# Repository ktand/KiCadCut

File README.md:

# About

Generate Silhouette Portrait/Cameo stencil cut file from Kicad PCB file.

Based on the work from [SMTCut](https://github.com/GatCode/SMTCut) and [gerber2graphtec](https://github.com/pmonta/gerber2graphtec)

## Setup

The project uses the [kicad_parser](https://github.com/realthunder/kicad_parser). To get this submodule, after checkout this repository, do

```
git submodule update --init --recursive
```

PDF output (`--pdf`) needs [fpdf2](https://github.com/py-pdf/fpdf2):

```
pip install -r requirements.txt
```

## Basic usage

### Generate cut file
```
kicadcut <kicad_pcb_file> <layer> >file.out
```

### Cuttning blade settings

For a 0.11mm film it appears that a blade setting of 0.15-0.17mm works fine for a 35 degree blade.

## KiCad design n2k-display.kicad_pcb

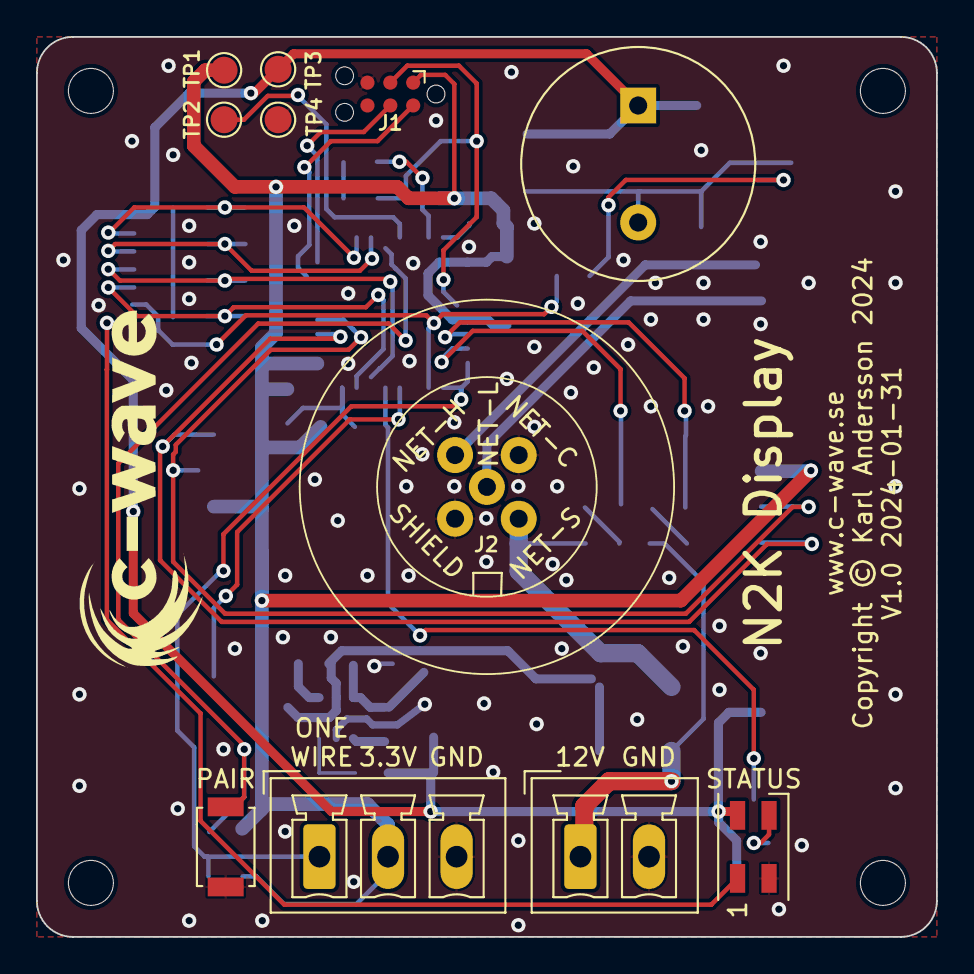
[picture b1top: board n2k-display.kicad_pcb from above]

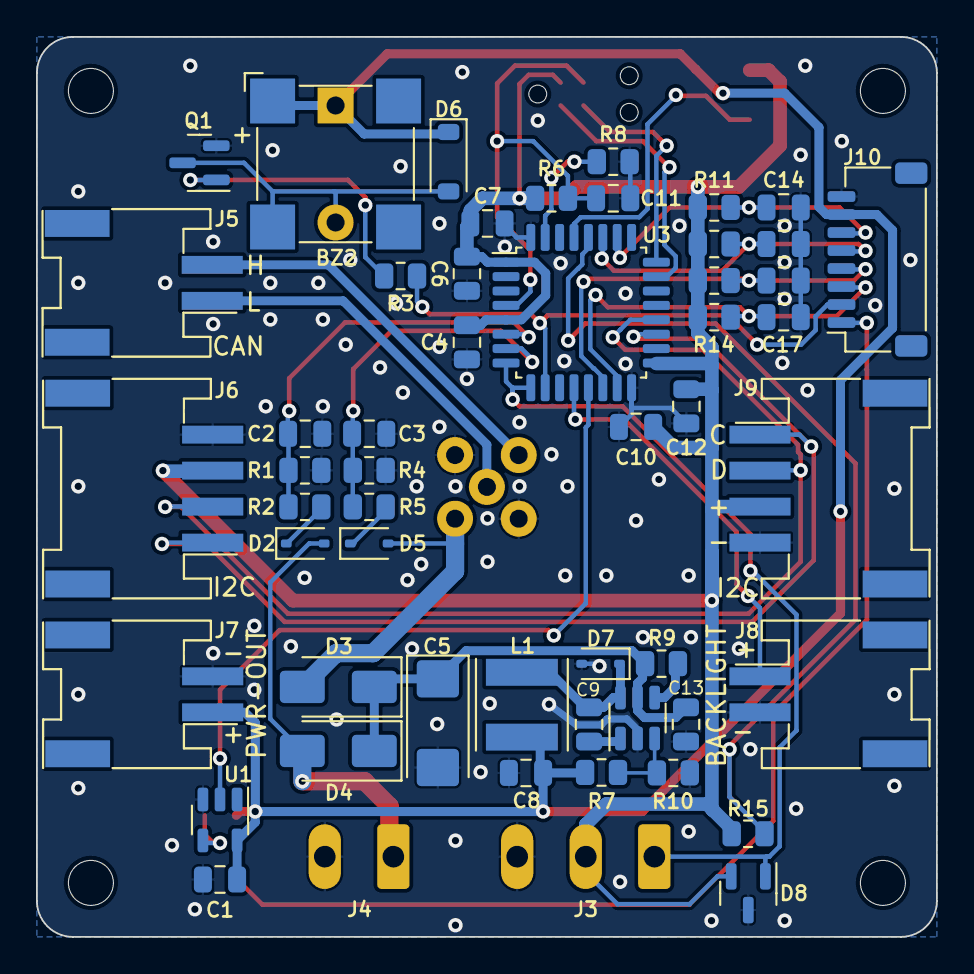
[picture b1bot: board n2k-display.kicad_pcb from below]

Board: 2 copper layers, 50.0 x 50.0 mm, 66 parts (51 on the bottom side), 36 nets.

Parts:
BZ1: 1255; Buzzer_1255
BZ2: CMT-8504-100-SMT-TR; MagneticBuzzer_CUI_CMT-8504-100-SMT
C1, C2, C3, C14, C15, C16, C17: 100n; C_0805_2012Metric
C4: 1uF; C_0805_2012Metric
C5: 100uF; CP_EIA-6032-28_Kemet-C
C6: 10nF; C_0805_2012Metric
C7, C9, C10, C11: 100nF; C_0805_2012Metric
C8: 10uF 16V X7R; C_0805_2012Metric
C12: 4.7uF; C_0805_2012Metric
C13: 10uF 35V X7R; C_0805_2012Metric
D1: SK6812MINI; LED_SK6812MINI_PLCC4_3.5x3.5mm_P1.75mm
D2, D5: SBA130CS-AU; D_SOD-323
D3: US1D; D_SMA
D4: B140-13F; D_SMA
D6: 1N4148W; D_SOD-123
D7: SBA130CS-AU (Schottky Vr > 16V VF >= 1A); D_SOD-323
D8: PESD3V3S2UT; SOT-23
H1, H2, H3, H4: MountingHole; MountingHole_2.5mm
J1: Conn_ARM_SWD_TagConnect_TC2030-NL; Tag-Connect_TC2030-IDC-NL_2x03_P1.27mm_Vertical
J2: NMEA2000; M12_Plug_Straight_5P_PCB
J3: One-Wire; PhoenixContact_MCV_1,5_3-G-3.81_1x03_P3.81mm_Vertical
J4: Battery; PhoenixContact_MCV_1,5_2-G-3.81_1x02_P3.81mm_Vertical
J5: CAN; HY2.0-2-SMD-90D (AliExpress)
J6: I2C-INT; HY2.0-4-SMD-90D (AliExpress)
J7: Power Out; HY2.0-2-SMD-90D (AliExpress)
J8: Backlight; HY2.0-2-SMD-90D (AliExpress)
J9: I2C-EXT; HY2.0-4-SMD-90D (AliExpress)
J10: KEYBOARD; JST_SH_SM08B-SRSS-TB_1x08-1MP_P1.00mm_Horizontal
L1: 22uH NRS5040T220MMGK; L_Taiyo-Yuden_NR-50xx
Q1: MMBT3904; SOT-23
R1, R4: 13.5K; R_0805_2012Metric
R2, R5, R9: 100K; R_0805_2012Metric
R3: 180; R_0805_2012Metric
R6, R8, R11, R12, R13, R14, R15: 10K; R_0805_2012Metric
R7: 49.9k; R_0805_2012Metric
R10: 15.8k; R_0805_2012Metric
SW1: SW_Push; SW_SPST_TS342A2P
TP1, TP2, TP3, TP4: TestPoint; TestPoint_Pad_D1.5mm
U1: SN74LV1T34DBV; SOT-23-5
U2: AOZ1282CI; SOT-23-6
U3: STM32F030K6Tx; LQFP-32_7x7mm_P0.8mm

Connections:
1-WIRE: D8.1 (A1), J3.1, U3.8 (PA2), U3.9 (PA3)
+3.3V: C4.1, C6.1, C7.1, C10.1, C12.1, D8.2 (A2), J1.1 (VCC), J3.2, J6.3, J9.3, R6.1, R11.1, R12.1, R13.1, R14.1, R15.1, TP1.1, U3.1 (VDD), U3.5 (VDDA), U3.17 (VDD)
+5V: BZ1.1 (+), BZ2.1 (+), C1.1, C8.1, D1.4 (VDD), D6.1 (K), J7.1, J10.7, L1.1, R7.1, TP3.1, U1.5 (VCC)
BACKLIGHT: J8.1, U3.12 (PA6)
BUTTON1: C14.1, J10.6, R11.2, U3.26 (PB3)
BUTTON2: C15.1, J10.5, R12.2, U3.27 (PB4)
BUTTON3: C16.1, J10.4, R13.2, U3.14 (PB0)
BUTTON4: C17.1, J10.3, R14.2, U3.15 (PB1)
BUZZER: J10.2, R3.1, U3.10 (PA4)
DBG-TX: TP2.1, U3.29 (PB6)
EXT-S: D2.2 (A), D4.2 (A), J4.1
EXT-VOLTAGE: C2.1, R1.2, R2.1, U3.6 (PA0)
GND: C1.2, C2.2, C3.2, C4.2, C5.2, C6.2, C7.2, C8.2, C10.2, C11.2, C12.2, C13.2, C14.2, C15.2, C16.2, C17.2, D1.2 (VSS), D7.2 (A), D8.3 (common), J1.5 (GND), J2.1, J2.3, J3.3, J4.2, J6.4, J7.2, J8.2, J9.4, J10.8, Q1.2 (E), R1.1, R4.1, R8.1, R10.2, SW1.1, TP4.1, U1.3 (GND), U2.2 (GND), U3.16 (VSS), U3.32 (VSS)
LED: U1.2 (A), U3.13 (PA7)
LED-OUT: D1.1 (DOUT), J10.1
NET+: J2.4, J5.2
NET-: J2.5, J5.1
NET-S: D3.2 (A), D5.2 (A), J2.2
NET-VOLTAGE: C3.1, R4.2, R5.1, U3.7 (PA1)
unnamed: BZ1.2 (-), BZ2.2 (-), D6.2 (A), Q1.3 (C)
unnamed: D1.3 (DIN), U1.4 (Y)
unnamed: D2.1 (K), R2.2
unnamed: C5.1, C13.1, D3.1 (K), D4.1 (K), R9.1, U2.5 (Vin)
unnamed: D5.1 (K), R5.2
unnamed: C9.2, D7.1 (K), L1.2, U2.6 (SW)
unnamed: Q1.1 (B), R3.2
unnamed: C9.1, U2.1 (BOOST)
unnamed: R9.2, U2.4 (EN)
unnamed: R7.2, R10.1, U2.3 (Vfb)
unnamed: R8.2, U3.31 (BOOT0)
PAIRING: R15.2, SW1.2, U3.28 (PB5)
RESET: C11.1, J1.3 (~RESET), R6.2, U3.4 (NRST)
SCL: J6.1, J9.1, U3.19 (PA9)
SDA: J6.2, J9.2, U3.20 (PA10)
SWCLK: J1.4 (SWCLK), U3.24 (PA14)
SWDIO: J1.2 (SWDIO), U3.23 (PA13)

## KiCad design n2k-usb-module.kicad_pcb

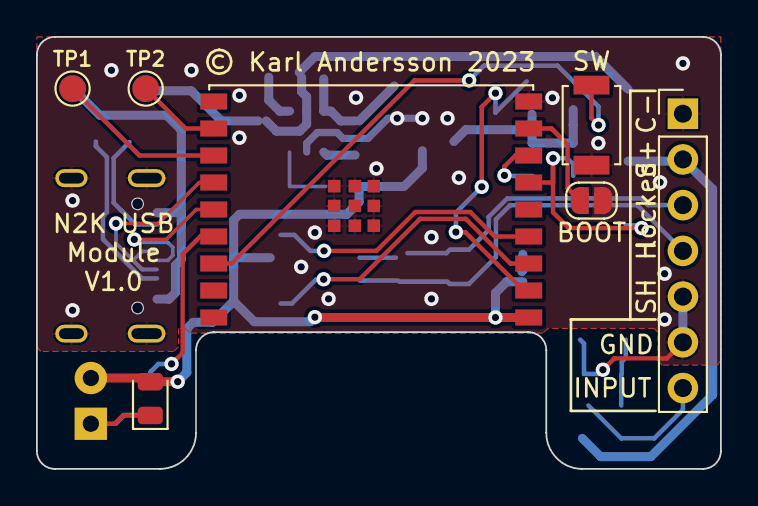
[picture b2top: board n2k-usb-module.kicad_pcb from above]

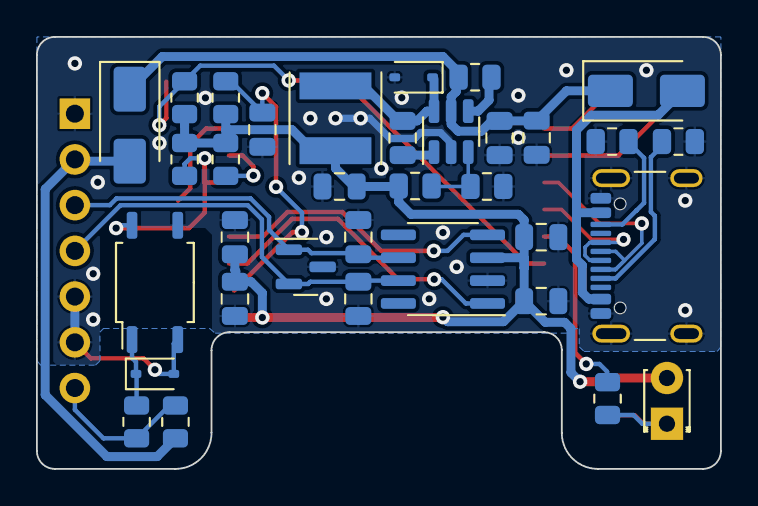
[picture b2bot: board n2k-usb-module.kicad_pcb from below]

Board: 2 copper layers, 38.0 x 24.0 mm, 41 parts (34 on the bottom side), 28 nets.

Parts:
C2, C10: 100nF; C_0805_2012Metric
C3: 10uF; C_0805_2012Metric
C4: 100n; C_0805_2012Metric
C5, C6: 15p; C_0805_2012Metric
C7: 10u; C_0805_2012Metric
C8: 470nF; C_0805_2012Metric
C9: 10uF 35V X7R; C_0805_2012Metric
C11: 10uF 16V X7R; C_0805_2012Metric
C12: 100nF 35V; C_0805_2012Metric
D1: 1N4148W; D_SOD-323
D2: LED; LED_0805_2012Metric
D3: LED; LED_D1.8mm_W3.3mm_H2.4mm
D7: PESD2IVN24-T; SOT-23
D8: SBA130CS-AU (Schottky Vr > 16V VF >= 1A); D_SOD-323
D9, D10: B140-13F; D_SMA
J3: Conn_01x07; PinHeader_1x07_P2.54mm_Vertical
J12: USB_C_Receptacle_USB2.0; USB_C_Receptacle_GCT_USB4105-xx-A_16P_TopMnt_Horizontal
JP1: BOOT; SolderJumper-2_P1.3mm_Open_RoundedPad1.0x1.5mm
L1: 22uH NRS5040T220MMGK; L_Taiyo-Yuden_NR-50xx
R1, R5: 4K7; R_0805_2012Metric
R2, R8, R9, R10: 10K; R_0805_2012Metric
R3, R4: 5K1; R_0805_2012Metric
R6: 1K; R_0805_2012Metric
R11: 100K; R_0805_2012Metric
R16: 49.9k; R_0805_2012Metric
R17: 15.8k; R_0805_2012Metric
SW1: SW_Push; SW_SPST_TS342A2P
TP1, TP2: TestPoint; TestPoint_Pad_D1.5mm
U1: ESP32-C3-MINI-1; ESP32-C3-WROOM-02
U2: SN65HVD232; SOIC-8_3.9x4.9mm_P1.27mm
U3: AOZ1282CI; SOT-23-6
U4: EL357; SOP-4_EL357

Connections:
+3.3V: C2.2, C3.2, C4.1, C7.1, C11.1, D2.2 (A), D3.2 (A), L1.1, R2.2, R8.1, R9.1, R10.1, R16.1, U1.1 (3V3), U2.3 (VCC)
+5V: D9.2 (A), J12.A4 (VBUS), J12.A9 (VBUS), J12.B4 (VBUS), J12.B9 (VBUS)
CAN-RX: U1.4 (GPIO5/ADC2_CH0), U2.4 (R)
CAN-TX: U1.3 (GPIO4/ADC1_CH4), U2.1 (D)
GND: C2.1, C3.1, C4.2, C5.1, C6.2, C7.2, C8.2, C9.2, C11.2, C12.2, D1.2 (A), D7.3 (common), D8.2 (A), J3.1, J3.5, J3.6, J12.A1 (GND), J12.A12 (GND), J12.B1 (GND), J12.B12 (GND), J12.S1 (SHIELD), JP1.2 (B), R3.2, R4.2, R17.2, SW1.2, U1.9 (GND), U1.19 (GND), U2.2 (GND), U3.2 (GND), U4.2, U4.3
IN: R2.1, U1.6 (GPIO7), U4.4
INPUT: J3.7, R1.2, R5.2
LED: R6.1, U1.15 (GPIO3/ADC1_CH3)
NET-H: C6.1, D7.2 (A2), J3.4, U2.7 (CANH)
NET-L: C5.2, D7.1 (A1), J3.3, U2.6 (CANL)
NET-S: D10.2 (A), J3.2, R5.1
unnamed: D1.1 (K), R1.1, U4.1
unnamed: D2.1 (K), D3.1 (K), R6.2
unnamed: C10.2, D8.1 (K), L1.2, U3.6 (SW)
unnamed: C9.1, C12.1, D9.1 (K), D10.1 (K), R11.1, U3.5 (Vin)
unnamed: J12.A5 (CC1), R3.1
unnamed: J12.B5 (CC2), R4.1
unnamed: JP1.1 (A), U1.8 (GPIO9)
unnamed: C8.1, R8.2, U1.2 (EN/CHIP_PU)
unnamed: R9.2, SW1.1, U1.16 (GPIO2/ADC1_CH2)
unnamed: R10.2, U1.7 (GPIO8)
unnamed: TP2.1, U1.11 (GPIO20/U0RXD)
unnamed: TP1.1, U1.12 (GPIO21/U0TXD)
unnamed: C10.1, U3.1 (BOOST)
unnamed: R11.2, U3.4 (EN)
unnamed: R16.2, R17.1, U3.3 (Vfb)
USB_D+: J12.A6 (D+), J12.B6 (D+), U1.14 (GPIO19/USB_D+)
USB_D-: J12.A7 (D-), J12.B7 (D-), U1.13 (GPIO18/USB_D-)

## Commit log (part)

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2023-11-17 First version pushed to GitHub
2023-11-18 Added shrink by percentage Added --file option
2024-02-05 Fixed pad orientation
2024-02-05 Reduced overcut compensation default
2024-02-07 Reduced default compensation Added defaults to helptext
2024-02-08 Fixed rotation

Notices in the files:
README.md:
GPL
n2k-display.kicad_pcb:
Copyright © Karl Andersson 2024
n2k-usb-module.kicad_pcb:
© Karl Andersson 2023
